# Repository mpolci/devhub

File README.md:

# devhub — hub USB "intelligente" per lo sviluppo hardware

Hub USB da banco pensato per chi sviluppa dispositivi a microcontrollore collegati via USB.
Oltre alle porte downstream espone all'host un **dispositivo di controllo** (USB HID) con cui
il PC può:

- **staccare e riattaccare fisicamente** ogni porta (alimentazione VBUS e linee dati D+/D-),
  per resettare un dispositivo bloccato anche quando il reset via USB non funziona;
- **leggere lo stato** di ogni porta (abilitata/disabilitata, ciclo in corso, guasti hardware);
- **comandare un relè ausiliario** con uscita su due boccole a banana (es. per sezionare
  l'alimentazione esterna del dispositivo in prova o chiudere un contatto di reset).

## Caratteristiche previste (v1)

| Voce | Scelta v1 |
|---|---|
| Porte downstream | 4 × USB-C |
| Velocità | USB 2.0 Hi-Speed (480 Mbit/s) |
| Alimentazione per porta | 5 V, fino a 2 A sulla singola porta USB-C, circa 2,4 A totali stimati, con limitazione di corrente e sezionamento per porta |
| Sezionamento | VBUS **e** D+/D− con unico comando logico; ammessa la sequenza interna del controller |
| Ciclo di spegnimento/riaccensione porta | Ciclo temporizzato con scarica attiva, durata configurabile; default indicativo 1 s da validare, senza verifica della tensione |
| Indicazione porta | Un LED dal MCU: spento, acceso fisso, lampeggiante per guasto |
| Alimentazione hub | richiesti alimentatore USB-C 5 V / 3 A senza negoziazione PD e cavo adeguato; nessuna verifica delle CC |
| Upstream (verso il PC) | USB-C (USB 2.0) |
| Controllo | STM32G0B1 su porta interna dell'hub, interfaccia USB HID senza driver + CLI Python |
| Relè ausiliari | 1 × SPDT su due boccole a banana COM/NC, contatti max 16 V / 3 A |
| Misure | Corrente e carica erogata per porta, temperatura del controllo; nessuna tensione |
| Pannello | 5 pulsanti; 5 LED: uno per porta USB, con lampeggio guasti, e uno di host collegato |

I 3 A d'ingresso comprendono anche i consumi interni: un sovraccarico complessivo può
interrompere l'intero hub. Il ciclo non verifica elettricamente lo spegnimento e riguarda
l'alimentazione fornita dalla porta; per riavviare schede autoalimentate servono relè o reset.

Le motivazioni delle scelte (in particolare USB 2.0 invece di USB 3 e il non sezionare GND)
sono in [docs/architettura.md](docs/architettura.md).

## Struttura del repository

```
docs/        requisiti, architettura, protocollo di controllo, domande aperte
hardware/    progetto KiCad (schema, PCB, BOM)
firmware/    firmware del MCU di controllo
host/        libreria Python e strumento da riga di comando per il PC, skill per agenti AI
```

## Documenti

- [docs/requisiti.md](docs/requisiti.md) — cosa deve fare il dispositivo
- [docs/architettura.md](docs/architettura.md) — schema a blocchi, scelte progettuali, componenti candidati, bilancio di potenza
- [docs/componenti.md](docs/componenti.md) — componenti candidati, package, fornitori, classe JLCPCB
- [docs/protocollo-controllo.md](docs/protocollo-controllo.md) — bozza del protocollo HID tra PC e hub
- [docs/regole-pcb.md](docs/regole-pcb.md) — stackup, piste, USB, alimentazione, piazzamento e verifiche di produzione
- [docs/pinout-mcu.md](docs/pinout-mcu.md) — piedinatura del MCU e note per il firmware
- [docs/domande-aperte.md](docs/domande-aperte.md) — decisioni ancora da prendere

## Licenze

- **Hardware** (`hardware/`): [CERN-OHL-W 2.0](hardware/LICENSE).
- **Firmware, libreria e CLI, documentazione** (tutto il resto): [MIT](LICENSE).

## Stato

Requisiti semplificati definiti (D60–D66). Hub USB2517I-JZX, MCU STM32G0B1CEU6 in UFQFPN48
(D78), due UCS2114-1-V/LX con due bus I²C e quattro PI3USB4002A per le porte (D75), con
DigiKey come fornitore di riferimento.

Schema elettrico v0.3 allineato ai requisiti (D79–D83); PCB 100 × 100 mm a quattro strati (D84)
completo (D84–D95, vedi [hardware/README.md](hardware/README.md)). Il prototipo Rev A è
montato e funziona: corretti alcuni difetti di saldatura, nessuna modifica al PCB.

Firmware ([firmware/README.md](firmware/README.md)) e libreria Python con CLI
([host/README.md](host/README.md)) sono scritti secondo D96–D103 e il protocollo 0.1. Sul
prototipo sono verificati hub configurato via SMBus, aggiornamento via DFU attraverso il
hub, le quattro porte (accensione, spegnimento, ciclo, enumerazione di un dispositivo),
relè, LED, pulsanti, default in flash, eventi, watchdog, temperatura del MCU e corrente delle porte. Restano le misure con strumenti:
durata della scarica e del ciclo, sfasamento delle accensioni, guasti reali e ritorno di
alimentazione (D98), tempi I²C, corrente dei LED, transitori al reset e in DFU. Dopo le misure
il protocollo passerà alla versione 1.0.

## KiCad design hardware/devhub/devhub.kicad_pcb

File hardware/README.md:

# hardware

Progetto KiCad 10 (schema, PCB, BOM) dell'hub.

```
hardware/devhub/        progetto KiCad: devhub.kicad_pro, devhub.kicad_sch (radice), i fogli e devhub.kicad_pcb
hardware/lib/           devhub.kicad_sym: simboli non presenti nelle librerie standard (USB2517, PI3USB4002A, TPS259470A, UCS2114) e SMAJ20A con pin K/A espliciti
hardware/devhub/production/   file di produzione Rev A: gerber (devhub_A.zip), BOM, posizioni, designatori, netlist IPC
hardware/devhub/jlcpcb/       database del plugin di esportazione per JLCPCB
```

## Stato: schema v0.3, PCB Rev A

Lo schema applica i [requisiti semplificati](../docs/requisiti.md) e le decisioni D60–D95
(dettaglio in D79): quattro porte USB-C, un relè, cinque pulsanti, un LED per porta, LED del relè e di host. Il PCB
da 100 × 100 mm è sbrogliato e prodotto come Rev A (vedi sotto).

Il prototipo Rev A è montato e collaudato con il firmware. Alimentazioni, hub, MCU, controller
delle porte, interruttori dati, LED, pulsanti e relè funzionano. Gli unici difetti trovati
erano saldature di U3 (MCU), U4 e U5 (UCS2114), J401 (connettore della porta 4) e U401 (switch
dati della porta 4), tutte ripassate. Nel PCB le reti sono corrette e non servono modifiche.
Dettaglio delle prove in
[../docs/lavorazioni/piano-firmware.md](../docs/lavorazioni/piano-firmware.md).

Simboli delle librerie standard di KiCad più quelli di progetto in `lib/`; fogli gerarchici riusati per le
porte. Componenti vicini collegati a filo, ma ogni rete ha comunque un nome esplicito: etichette
locali per le reti interne a un foglio, globali per quelle che passano tra fogli, gerarchiche per
le porte. Passa l'ERC di `kicad-cli` con zero violazioni.

Fogli:

| Foglio | Contenuto |
|---|---|
| `power_in` | USB-C di alimentazione a 5 V, Rd 5,1 kΩ su CC1/CC2 senza lettura, TVS, eFuse TPS259470A (U13), bulk, Schottky D2, LDO 3,3 V (AP7361C-33E, SOT-223) |
| `hub` | USB2517, USB-C upstream con ESD, quarzo, RBIAS, supervisore di reset (U12) in wired-OR con il MCU, strap di configurazione, VBUS_DET; DS5, DS7 e OCS5_N non collegati. Switch VBUS: 2 × UCS2114-1-V/LX (U4 porte 1-2 su I2C1, U5 porte 3-4 su I2C2), strap COMM_ILIM 27 kΩ, disaccoppiamenti, pull-up degli ALERT# |
| `mcu` | STM32G0B1CEU6 (UFQFPN48), decoupling, SWD (J4) e UART (J9) collegati a filo, pull-up dei due bus I²C, pull-down degli EN porta, pull-down dei DBCC dell'UCPD, LED di host collegato |
| `port_c` ×4 | connettore, switch dati PI3USB4002A (con protezione ESD integrata), condensatori VBUS, Rp 56 kΩ, LED verde dal MCU, pulsante |
| `relays` | ULN2003V12 (3 canali in parallelo), G5Q-1, ponticello NC/NO, boccole Cliff FCR7350, snubber DNP, pulsante SW1, LED del relè D90 |

Piedinatura del MCU: [../docs/pinout-mcu.md](../docs/pinout-mcu.md).

Connettori USB decisi (D18): GCT USB4105-GF-A per tutti gli USB-C.

Quarzo deciso (D19): YXC X322524MOB4SI, C_L 12 pF, C22/C23 da 15 pF.

Footprint locali assegnati dalla libreria `lcsc_footprints` (`devhub/libs/footprints.pretty`):
- U13 TPS259470A: `C3662799_VQFN-10_L2_0-W2_0-P0_45-TL`;
- U101–U401 PI3USB4002A: `C3657361_UQFN-10_L2_0-W1_5-P0_50-TL`;
- U4, U5 UCS2114: `UCS2114_VQFN-20_3x3mm_P0.5mm`;
- U2 USB2517: `QFN-64-1EP_9x9mm_P0.5mm_EP4.7x4.7mm_ThermalVias_0.3mm` (D50).

Le piazzole di U13 e U101–U401 sono quelle generate da LCSC, non copiate dai land pattern dei
costruttori: nel PI3USB4002A le laterali sono 0,665 × 0,28 mm invece di 0,53 × 0,25 (più lunghe
verso l'esterno, stesso bordo interno), nel TPS259470A le coordinate coincidono con l'esempio TI
RPW0010A entro ~0,05 mm. Differenze accettate: il bordo esterno più lungo aiuta la saldatura ad
aria calda. Courtyard ridisegnati a 0,25 mm dalle piazzole (quelli importati erano più piccoli
del rame).

L'impronta dell'UCS2114 segue il land pattern Microchip C04-2421 Rev C (datasheet
DS20005743B): 20 piazzole 0,25 × 0,5 mm su C1 = C2 = 2,9 mm, otto angoli smussati di 0,1 mm,
area termica 2,00 × 1,13 mm coperta da solder mask e collegata al pin 17 (GND), con 6 via
0,3/0,5 mm. Il package non ha pad esposto. Modello 3D: quello di KiCad per UFQFPN-20 3 × 3 mm,
come segnaposto (stesse dimensioni in pianta, altezza diversa).

J4 (SWD, Samtec FTSH-105-01-L-DV-K) usa l'impronta generica
`PinHeader_2x05_P1.27mm_Vertical_SMD`: KiCad non ha quella Samtec, e rispetto al land pattern
Samtec le piazzole sono più corte (2,40 invece di 2,79 mm, ingombro 6,30 invece di 6,86 mm), con
stesso passo e stessa larghezza. Accettata: è un connettore di debug saldato a mano.

I footprint usano i modelli in `devhub/libs/3dmodels` con percorsi relativi al progetto.
Il modello C3657361 è un segnaposto dell'importatore, non una rappresentazione del package.

BOM: i simboli hanno i campi `warehouse` (ID del magazzino), `lcsc`, `mouser` e `digikey`;
confronto dei costi della v0.2 in [../docs/confronto-costi.md](../docs/confronto-costi.md). Su
Mouser mancano le boccole Cliff (campo vuoto). Da completare: U4/U5 (nessun codice fornitore),
U3 su Mouser e LCSC, R60/R61 su LCSC.

Per l'ERC da riga di comando:

```bash
/Applications/KiCad/KiCad.app/Contents/MacOS/kicad-cli sch erc --severity-all --output /tmp/erc.rpt hardware/devhub/devhub.kicad_sch
```

## PCB

Regole di progettazione: [stackup, routing e verifiche PCB](../docs/regole-pcb.md), configurate
nel progetto: stackup nel PCB, vincoli e netclass in `devhub.kicad_pro`, regole personalizzate in
`devhub.kicad_dru`.

`devhub.kicad_pcb`: 4 strati, profilo **100 × 100 mm** con angoli R3 (D84), allineato allo schema
v0.3 (parità senza differenze). Vista dall'alto, fronte (lato banco) in basso; u dal bordo
sinistro, v dal bordo frontale.

| Cosa | Faccia | Posizione (u, v in mm) |
|---|---|---|
| J5 COM, J6 NC boccole | inferiore | u = 10 e 27; corpo a v = 11,85 come prima, manicotto a filo della faccia esterna della parete |
| J401, J301, J201, J101 USB-C (porte 4…1) | inferiore | u = 46, 61, 76, 91; faccia d'innesto a filo del bordo frontale |
| LED delle porte D402…D102 (verdi) | superiore | in asse con la porta, v = 2 |
| D90 LED relè | superiore | u = 18,5, v = 2, sopra la coppia di boccole (D90) |
| D93 LED host | superiore | u = 10, v = 90, sul retro a sinistra di J1, con R93 a u = 15 (D90) |
| SW1, SW401…SW101 pulsanti | superiore | v = 14,5 (D87); SW1 al centro delle boccole (u = 18,5), gli altri in asse con le porte |
| J1 alimentazione, J2 upstream | inferiore | u = 24 e 82, a filo del bordo posteriore |
| H1–H4 fori M3 | — | H1 (20; 44,2) a destra del relè K1, dentro l'area dei contatti (D95), H2 (95,5; 28), H3 (4,5; 95,5), H4 (95,5; 95,5); anello di rame da 6,4 mm, senza rete |

Gruppi funzionali sulla faccia inferiore, traslati dal piazzamento v0.2 con le rispettive aree
di regola: porte con switch dati e condensatori dietro i connettori; U4/U5 UCS2114 dietro i
pulsanti, fra le porte che servono; relè K1, driver U9 e ponticello a sinistra dietro le boccole;
MCU al centro; hub con quarzo e disaccoppiamenti al centro-destra; alimentazione (eFuse, LDO,
bulk) dietro a sinistra; upstream con ESD e VBUS_DET dietro a destra; J4 (SWD) e J9 (UART) sul
retro, fra J1 e J2.

Sbroglio completo. Piani: GND su In2.Cu (`GND_In2`), +3V3 su In1.Cu (`3V3_In1`) con isole VBUS
sotto i connettori e una zona +5V lungo il bordo frontale verso U4/U5 (D93). Il PCB va
modificato in KiCad dallo stato corrente, non rigenerato.

Per il controllo di parità con lo schema da riga di comando:

```bash
/Applications/KiCad/KiCad.app/Contents/MacOS/kicad-cli pcb drc --schematic-parity --severity-all --output /tmp/drc.rpt hardware/devhub/devhub.kicad_pcb
```

I datasheet dei componenti sono in `../datasheets/` (fuori dal repository: non ridistribuibili).
Da scaricare a mano dal sito ST, che blocca i download automatici: datasheet STM32G0B1, reference
manual RM0444, datasheet USBLC6-2.

Licenza: CERN-OHL-W 2.0, vedi [LICENSE](LICENSE).

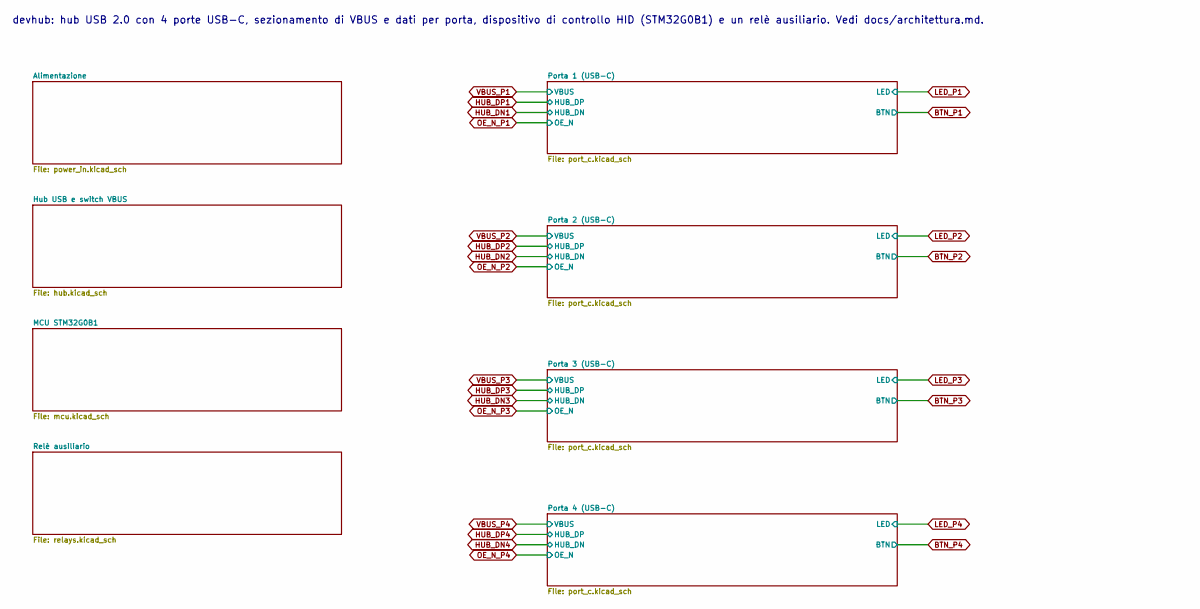
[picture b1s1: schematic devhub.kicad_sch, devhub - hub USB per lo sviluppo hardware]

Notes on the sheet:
devhub: hub USB 2.0 con 4 porte USB-C, sezionamento di VBUS e dati per porta, dispositivo di controllo HID (STM32G0B1) e un relè ausiliario. Vedi docs/architettura.md.

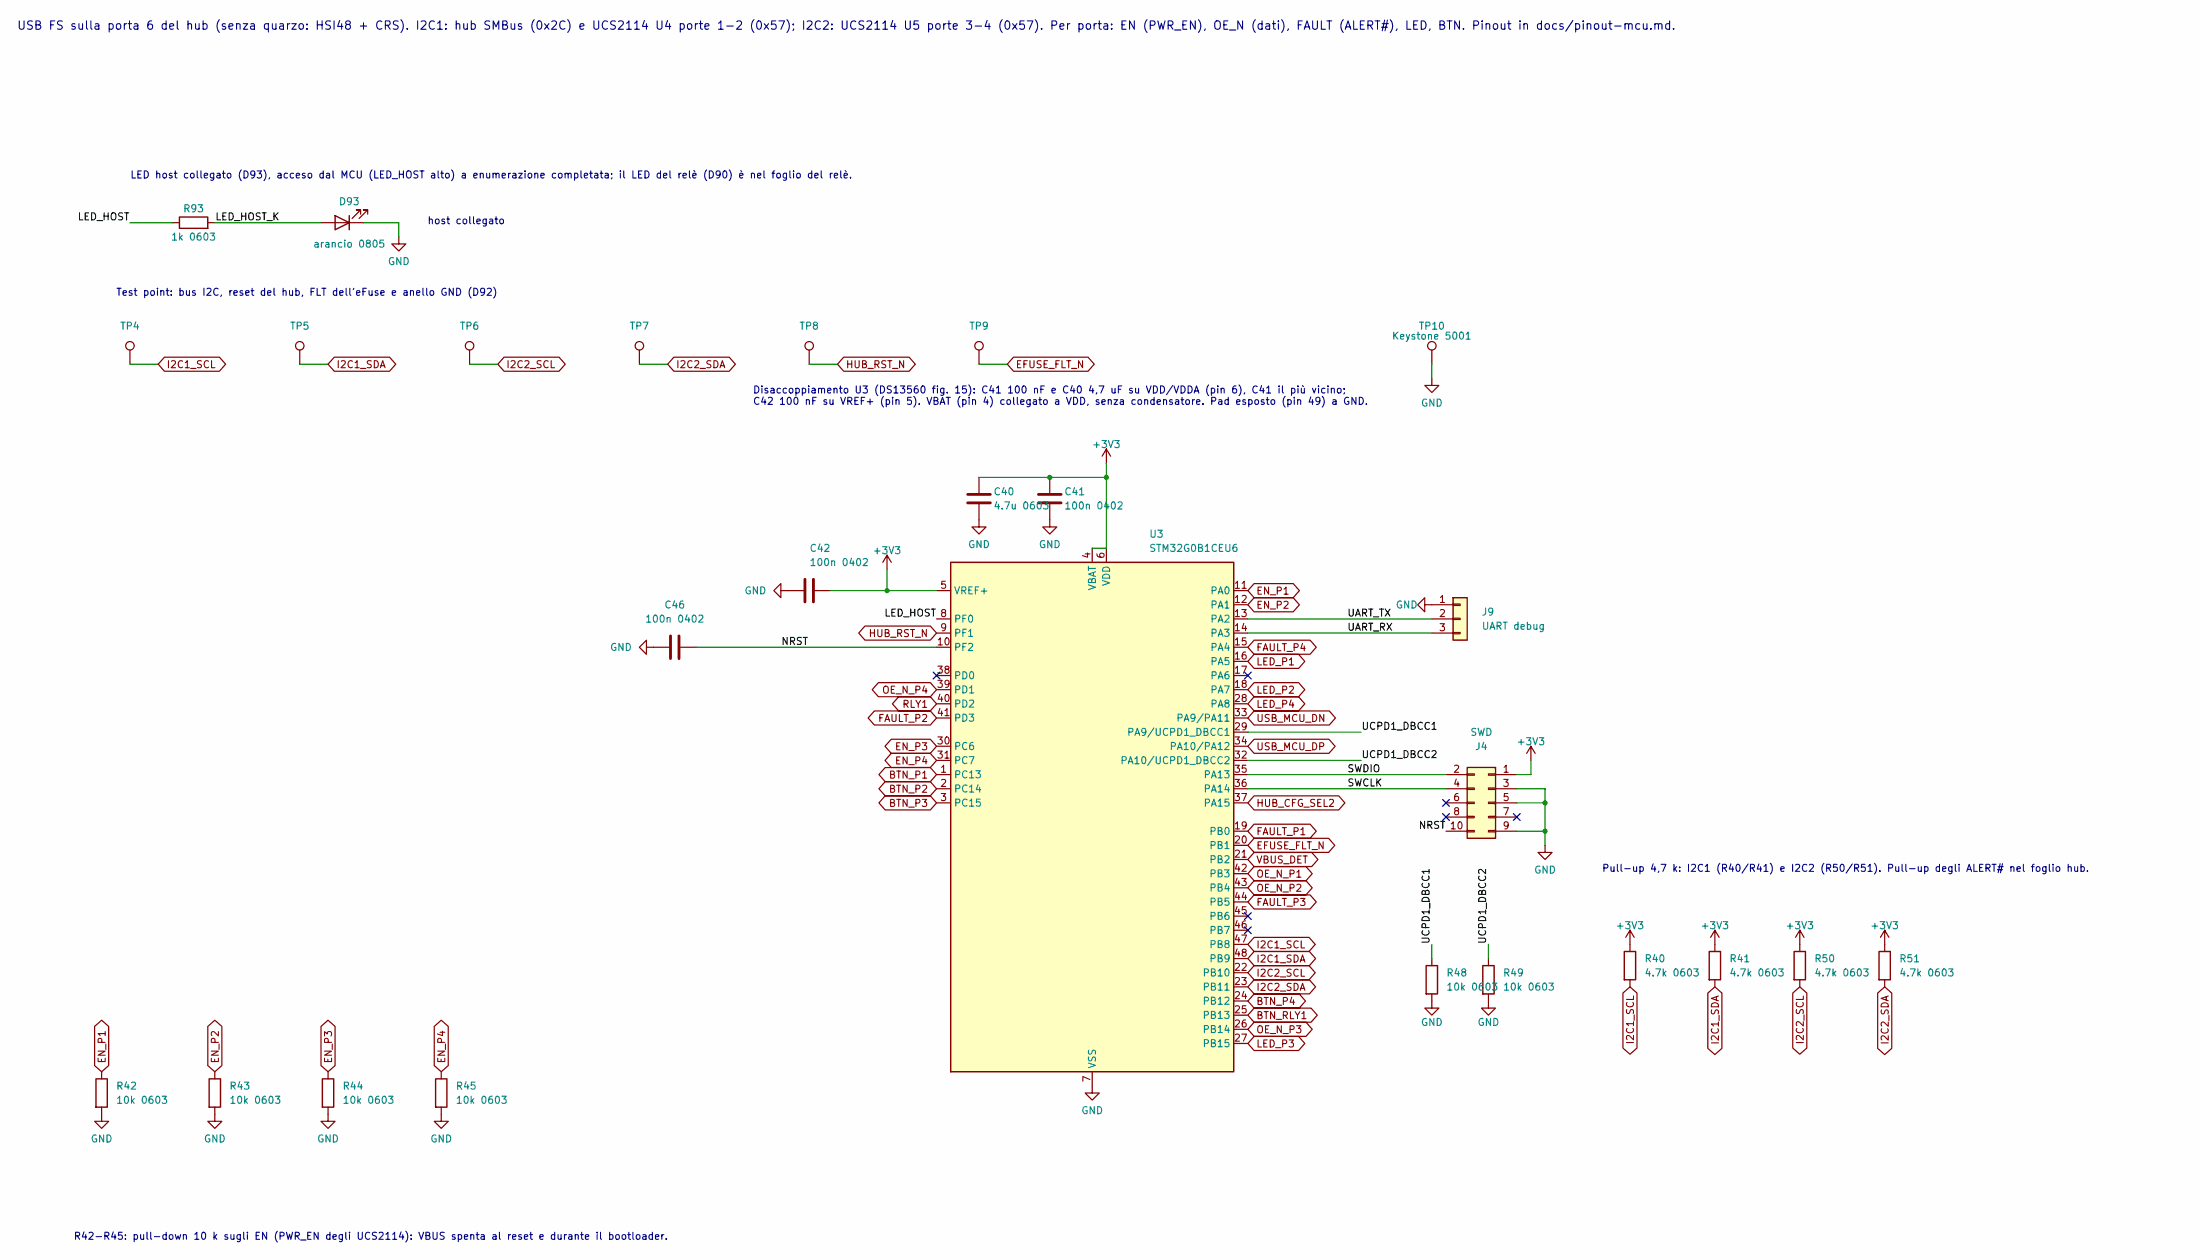
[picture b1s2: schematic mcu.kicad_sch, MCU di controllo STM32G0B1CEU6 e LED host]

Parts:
C40: 4.7u 0603; C_0603_1608Metric; MPN lcsc CL10A475KO8NNNC; lcsc C19666
C41, C42, C46: 100n 0402; C_0402_1005Metric; MPN lcsc CC0402KRX7R7BB104; lcsc C60474
D93: arancio 0805; LED_0805_2012Metric; MPN lcsc LTST-C171KFKT; lcsc C284932
J4: SWD; PinHeader_2x05_P1.27mm_Vertical_SMD; MPN lcsc FTSH-105-01-L-DV-K; lcsc C5155080
J9: UART debug; PinHeader_1x03_P2.54mm_Vertical; MPN lcsc 2.54-1*3P; lcsc C49257
R40, R41, R50, R51: 4.7k 0603; R_0603_1608Metric; MPN lcsc RC0603FR-074K7L; lcsc C99782
R42, R43, R44, R45, R48, R49: 10k 0603; R_0603_1608Metric; MPN lcsc FRC0603F1002TS; lcsc C2906982
R93: 1k 0603; R_0603_1608Metric; MPN lcsc 0603WAF1001T5E; lcsc C21190
TP4: I2C1_SCL; TestPoint_Pad_D1.5mm
TP5: I2C1_SDA; TestPoint_Pad_D1.5mm
TP6: I2C2_SCL; TestPoint_Pad_D1.5mm
TP7: I2C2_SDA; TestPoint_Pad_D1.5mm
TP8: HUB_RST_N; TestPoint_Pad_D1.5mm
TP9: EFUSE_FLT_N; TestPoint_Pad_D1.5mm
TP10: Keystone 5001; TestPoint_Keystone_5000-5004_Miniature; MPN mouser 5001; lcsc C238122
U3: STM32G0B1CEU6; QFN-48-1EP_7x7mm_P0.5mm_EP5.6x5.6mm; MPN lcsc STM32G0B1CEU6; lcsc C2829190

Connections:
+3V3: C40.1, C41.1, C42.1, J4.1, R40.1, R41.1, R50.1, R51.1, U3.4 (VBAT), U3.5 (VREF+), U3.6 (VDD); also elsewhere on the board
/MCU STM32G0B1/LED_HOST: R93.1, U3.8 (PF0)
/MCU STM32G0B1/LED_HOST_K: D93.2 (A), R93.2
/MCU STM32G0B1/NRST: C46.1, J4.10, U3.10 (PF2)
/MCU STM32G0B1/SWCLK: J4.4, U3.36 (PA14)
/MCU STM32G0B1/SWDIO: J4.2, U3.35 (PA13)
/MCU STM32G0B1/UART_RX: J9.3, U3.14 (PA3)
/MCU STM32G0B1/UART_TX: J9.2, U3.13 (PA2)
/MCU STM32G0B1/UCPD1_DBCC1: R48.1, U3.29 (PA9/UCPD1_DBCC1)
/MCU STM32G0B1/UCPD1_DBCC2: R49.1, U3.32 (PA10/UCPD1_DBCC2)
BTN_P1: U3.1 (PC13); also elsewhere on the board
BTN_P2: U3.2 (PC14); also elsewhere on the board
BTN_P3: U3.3 (PC15); also elsewhere on the board
BTN_P4: U3.24 (PB12); also elsewhere on the board
BTN_RLY1: U3.25 (PB13); also elsewhere on the board
EFUSE_FLT_N: TP9.1 (1_1), U3.20 (PB1); also elsewhere on the board
EN_P1: R42.1, U3.11 (PA0); also elsewhere on the board
EN_P2: R43.1, U3.12 (PA1); also elsewhere on the board
EN_P3: R44.1, U3.30 (PC6); also elsewhere on the board
EN_P4: R45.1, U3.31 (PC7); also elsewhere on the board
FAULT_P1: U3.19 (PB0); also elsewhere on the board
FAULT_P2: U3.41 (PD3); also elsewhere on the board
FAULT_P3: U3.44 (PB5); also elsewhere on the board
FAULT_P4: U3.15 (PA4); also elsewhere on the board
GND: C40.2, C41.2, C42.2, C46.2, D93.1 (K), J4.3, J4.5, J4.9, J9.1, R42.2, R43.2, R44.2, R45.2, R48.2, R49.2, TP10.1 (1_1), U3.7 (VSS), U3.49 (VSS); also elsewhere on the board
HUB_CFG_SEL2: U3.37 (PA15); also elsewhere on the board
HUB_RST_N: TP8.1 (1_1), U3.9 (PF1); also elsewhere on the board
I2C1_SCL: R40.2, TP4.1 (1_1), U3.47 (PB8); also elsewhere on the board
I2C1_SDA: R41.2, TP5.1 (1_1), U3.48 (PB9); also elsewhere on the board
I2C2_SCL: R50.2, TP6.1 (1_1), U3.22 (PB10); also elsewhere on the board
I2C2_SDA: R51.2, TP7.1 (1_1), U3.23 (PB11); also elsewhere on the board
LED_P1: U3.16 (PA5); also elsewhere on the board
LED_P2: U3.18 (PA7); also elsewhere on the board
LED_P3: U3.27 (PB15); also elsewhere on the board
LED_P4: U3.28 (PA8); also elsewhere on the board
OE_N_P1: U3.42 (PB3); also elsewhere on the board
OE_N_P2: U3.43 (PB4); also elsewhere on the board
OE_N_P3: U3.26 (PB14); also elsewhere on the board
OE_N_P4: U3.39 (PD1); also elsewhere on the board
RLY1: U3.40 (PD2); also elsewhere on the board
USB_MCU_DN: U3.33 (PA9/PA11); also elsewhere on the board
USB_MCU_DP: U3.34 (PA10/PA12); also elsewhere on the board
VBUS_DET: U3.21 (PB2); also elsewhere on the board

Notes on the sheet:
Disaccoppiamento U3 (DS13560 fig. 15): C41 100 nF e C40 4,7 uF su VDD/VDDA (pin 6), C41 il più vicino; C42 100 nF su VREF+ (pin 5). VBAT (pin 4) collegato a VDD, senza condensatore. Pad esposto (pin 49) a GND.
Test point: bus I2C, reset del hub, FLT dell'eFuse e anello GND (D92)
USB FS sulla porta 6 del hub (senza quarzo: HSI48 + CRS). I2C1: hub SMBus (0x2C) e UCS2114 U4 porte 1-2 (0x57); I2C2: UCS2114 U5 porte 3-4 (0x57). Per porta: EN (PWR_EN), OE_N (dati), FAULT (ALERT#), LED, BTN. Pinout in docs/pinout-mcu.md.
Pull-up 4,7 k: I2C1 (R40/R41) e I2C2 (R50/R51). Pull-up degli ALERT# nel foglio hub.
host collegato
LED host collegato (D93), acceso dal MCU (LED_HOST alto) a enumerazione completata; il LED del relè (D90) è nel foglio del relè.
R42-R45: pull-down 10 k sugli EN (PWR_EN degli UCS2114): VBUS spenta al reset e durante il bootloader.

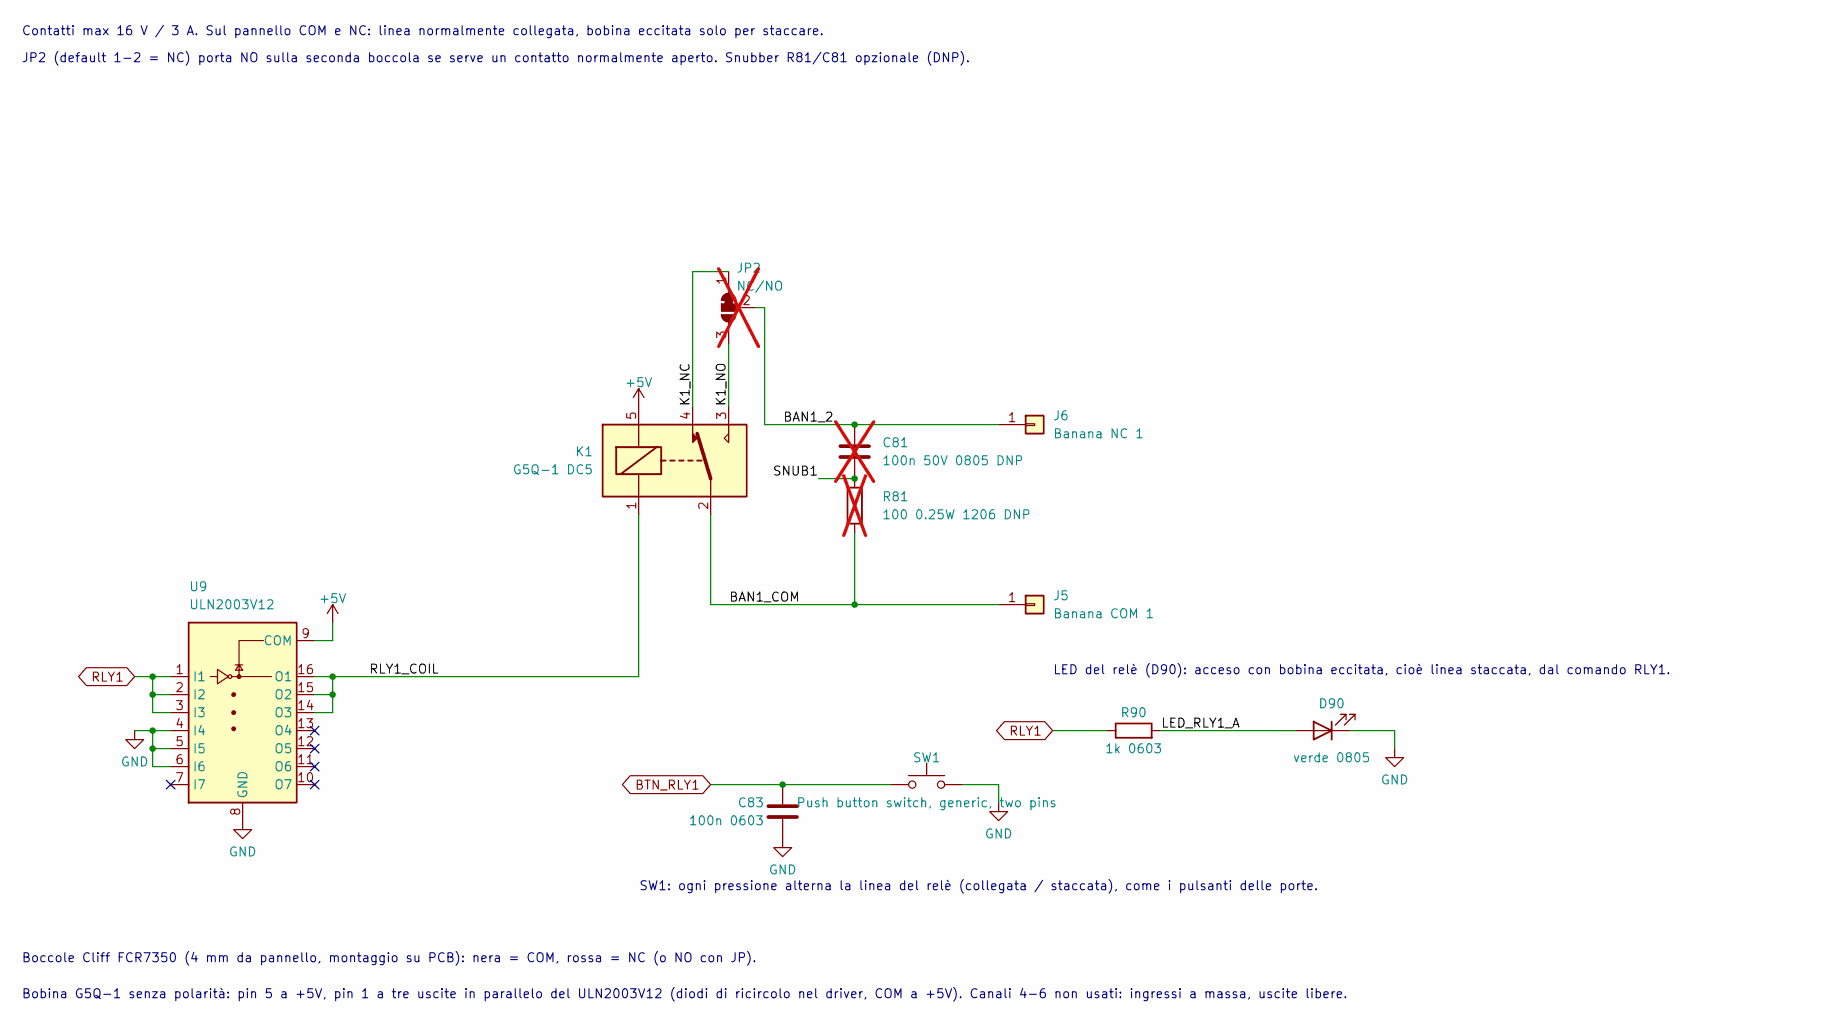
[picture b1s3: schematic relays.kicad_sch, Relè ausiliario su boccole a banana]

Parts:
C81: 100n 50V 0805 DNP; C_0805_2012Metric; MPN lcsc 0805B104K500CT; lcsc C83055; not fitted
C83: 100n 0603; C_0603_1608Metric; MPN lcsc CL10B104KB8NNNC; lcsc C1591
D90: verde 0805; LED_0805_2012Metric; MPN lcsc LTST-C171GKT; lcsc C913075
J5: Banana COM 1; Banana_Cliff_FCR7350B_S16N-PC_Horizontal; MPN digikey FCR7350B; digikey 4654-FCR7350B-ND
J6: Banana NC 1; Banana_Cliff_FCR7350R_S16N-PC_Horizontal; MPN lcsc FCR7350R; lcsc C6041087
JP2: NC/NO; SolderJumper-3_P2.4mm_Bridged12_Pad2.0x3.0mm; not fitted
K1: G5Q-1 DC5; Relay_SPDT_Omron-G5Q-1; MPN lcsc G5Q-14 DC5; lcsc C397241
R81: 100 0.25W 1206 DNP; R_1206_3216Metric; MPN lcsc RC1206FR-07100RL; lcsc C137392; not fitted
R90: 1k 0603; R_0603_1608Metric; MPN lcsc 0603WAF1001T5E; lcsc C21190
SW1: Push button switch, generic, two pins; SW_SPST_PTS645Sx43SMTR92; MPN lcsc PTS645SL70SMTR92 LFS; lcsc C285485
U9: ULN2003V12; SOIC-16_3.9x9.9mm_P1.27mm; MPN lcsc ULN2003V12DR; lcsc C94916

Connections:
+5V: K1.5, U9.9 (COM); also elsewhere on the board
/Relè ausiliario/BAN1_2: C81.1, J6.1 (Pin_1_1), JP2.2 (C)
/Relè ausiliario/BAN1_COM: J5.1 (Pin_1_1), K1.2, R81.2
/Relè ausiliario/K1_NC: JP2.1 (A), K1.4
/Relè ausiliario/K1_NO: JP2.3 (B), K1.3
/Relè ausiliario/LED_RLY1_A: D90.2 (A), R90.2
/Relè ausiliario/RLY1_COIL: K1.1, U9.14 (O3), U9.15 (O2), U9.16 (O1)
/Relè ausiliario/SNUB1: C81.2, R81.1
BTN_RLY1: C83.1, SW1.1; also elsewhere on the board
GND: C83.2, D90.1 (K), SW1.2, U9.4 (I4), U9.5 (I5), U9.6 (I6), U9.8 (GND); also elsewhere on the board
RLY1: R90.1, U9.1 (I1), U9.2 (I2), U9.3 (I3); also elsewhere on the board

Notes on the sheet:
Bobina G5Q-1 senza polarità: pin 5 a +5V, pin 1 a tre uscite in parallelo del ULN2003V12 (diodi di ricircolo nel driver, COM a +5V). Canali 4-6 non usati: ingressi a massa, uscite libere.
JP2 (default 1-2 = NC) porta NO sulla seconda boccola se serve un contatto normalmente aperto. Snubber R81/C81 opzionale (DNP).
Boccole Cliff FCR7350 (4 mm da pannello, montaggio su PCB): nera = COM, rossa = NC (o NO con JP).
Contatti max 16 V / 3 A. Sul pannello COM e NC: linea normalmente collegata, bobina eccitata solo per staccare.
LED del relè (D90): acceso con bobina eccitata, cioè linea staccata, dal comando RLY1.
SW1: ogni pressione alterna la linea del relè (collegata / staccata), come i pulsanti delle porte.

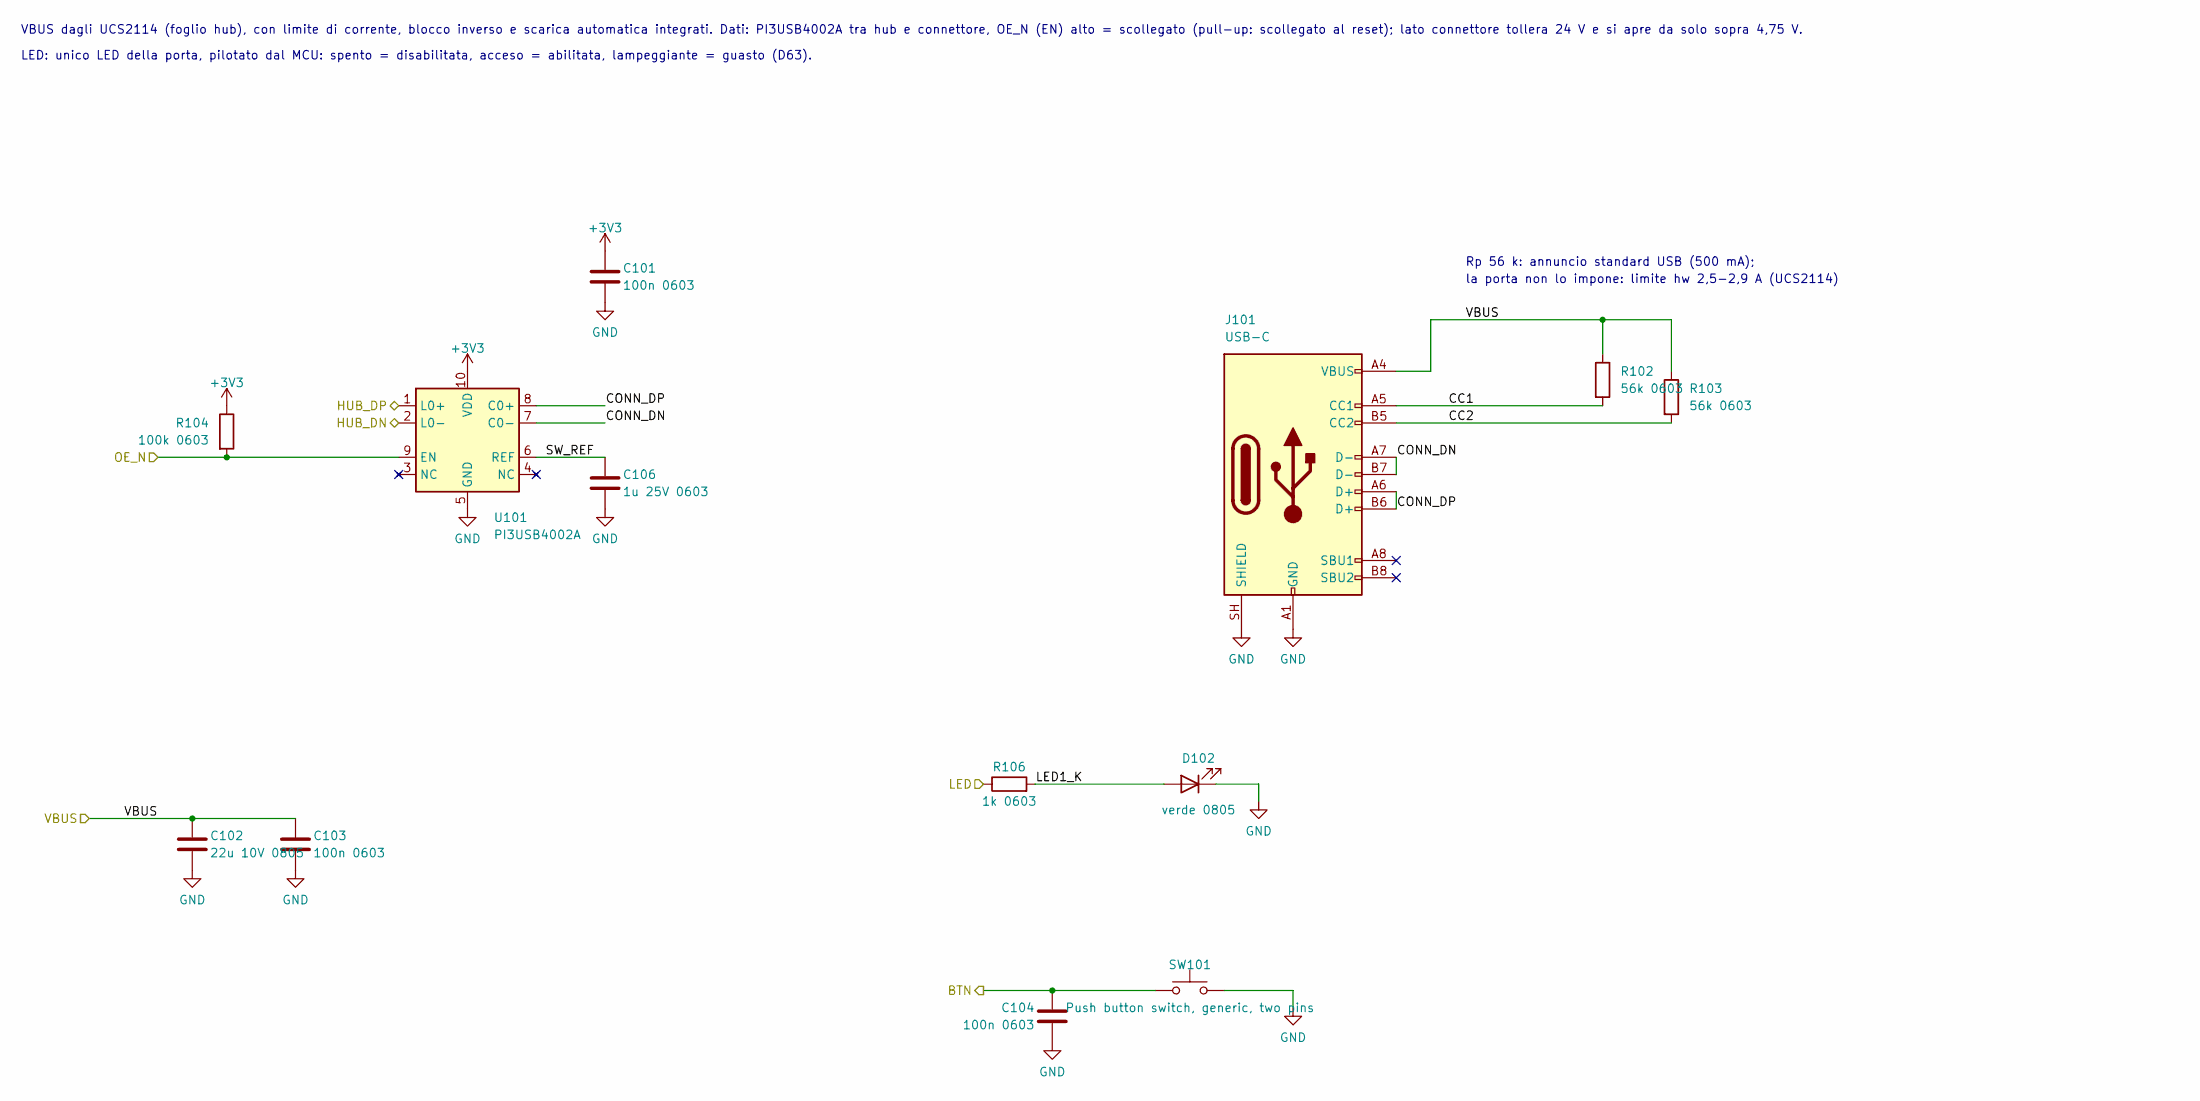
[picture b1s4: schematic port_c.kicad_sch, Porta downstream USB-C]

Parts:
C101, C103, C104: 100n 0603; C_0603_1608Metric; MPN lcsc CL10B104KB8NNNC; lcsc C1591
C102: 22u 10V 0805; C_0805_2012Metric; MPN lcsc GRM21BZ71A226ME15L; lcsc C907991
C106: 1u 25V 0603; C_0603_1608Metric; MPN lcsc CL10B105KA8NNNC; lcsc C29936
D102: verde 0805; LED_0805_2012Metric; MPN lcsc LTST-C171GKT; lcsc C913075
J101: USB-C; USB_C_Receptacle_GCT_USB4105-xx-A_16P_TopMnt_Horizontal; MPN lcsc USB4105-GF-A; lcsc C3020560
R102, R103: 56k 0603; R_0603_1608Metric; MPN lcsc RC0603FR-0756KL; lcsc C114630
R104: 100k 0603; R_0603_1608Metric; MPN lcsc FRC0603F1003TS; lcsc C2906980
R106: 1k 0603; R_0603_1608Metric; MPN lcsc 0603WAF1001T5E; lcsc C21190
SW101: Push button switch, generic, two pins; SW_SPST_PTS645Sx43SMTR92; MPN lcsc PTS645SL70SMTR92 LFS; lcsc C285485
U101: PI3USB4002A; C3657361_UQFN-10_L2_0-W1_5-P0_50-TL; MPN lcsc PI3USB4002AZUAEX; lcsc C6735706

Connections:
+3V3: C101.1, R104.1, U101.10 (VDD); also elsewhere on the board
/Porta 1 (USB-C)/CC1: J101.A5 (CC1), R102.2
/Porta 1 (USB-C)/CC2: J101.B5 (CC2), R103.2
/Porta 1 (USB-C)/CONN_DN: J101.A7 (D-), J101.B7 (D-), U101.7 (C0-)
/Porta 1 (USB-C)/CONN_DP: J101.A6 (D+), J101.B6 (D+), U101.8 (C0+)
/Porta 1 (USB-C)/LED1_K: D102.2 (A), R106.2
/Porta 1 (USB-C)/SW_REF: C106.1, U101.6 (REF)
BTN_P1: C104.1, SW101.1; also elsewhere on the board
GND: C101.2, C102.2, C103.2, C104.2, C106.2, D102.1 (K), J101.A1 (GND), J101.A12 (GND), J101.B1 (GND), J101.B12 (GND), J101.SH (SHIELD), SW101.2, U101.5 (GND); also elsewhere on the board
HUB_DN1: U101.2 (L0-); also elsewhere on the board
HUB_DP1: U101.1 (L0+); also elsewhere on the board
LED_P1: R106.1; also elsewhere on the board
OE_N_P1: R104.2, U101.9 (EN); also elsewhere on the board
VBUS_P1: C102.1, C103.1, J101.A4 (VBUS), J101.A9 (VBUS), J101.B4 (VBUS), J101.B9 (VBUS), R102.1, R103.1; also elsewhere on the board

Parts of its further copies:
C201, C203, C204, C301, C303, C304, C401, C403, C404: 100n 0603; C_0603_1608Metric; MPN lcsc CL10B104KB8NNNC; lcsc C1591
C202, C302, C402: 22u 10V 0805; C_0805_2012Metric; MPN lcsc GRM21BZ71A226ME15L; lcsc C907991
C206, C306, C406: 1u 25V 0603; C_0603_1608Metric; MPN lcsc CL10B105KA8NNNC; lcsc C29936
D202, D302, D402: verde 0805; LED_0805_2012Metric; MPN lcsc LTST-C171GKT; lcsc C913075
J201, J301, J401: USB-C; USB_C_Receptacle_GCT_USB4105-xx-A_16P_TopMnt_Horizontal; MPN lcsc USB4105-GF-A; lcsc C3020560
R202, R203, R302, R303, R402, R403: 56k 0603; R_0603_1608Metric; MPN lcsc RC0603FR-0756KL; lcsc C114630
R204, R304, R404: 100k 0603; R_0603_1608Metric; MPN lcsc FRC0603F1003TS; lcsc C2906980
R206, R306, R406: 1k 0603; R_0603_1608Metric; MPN lcsc 0603WAF1001T5E; lcsc C21190
SW201, SW301, SW401: Push button switch, generic, two pins; SW_SPST_PTS645Sx43SMTR92; MPN lcsc PTS645SL70SMTR92 LFS; lcsc C285485
U201, U301, U401: PI3USB4002A; C3657361_UQFN-10_L2_0-W1_5-P0_50-TL; MPN lcsc PI3USB4002AZUAEX; lcsc C6735706

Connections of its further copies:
+3V3: C201.1, C301.1, C401.1, R204.1, R304.1, R404.1, U201.10 (VDD), U301.10 (VDD), U401.10 (VDD); also elsewhere on the board
/Porta 2 (USB-C)/CC1: J201.A5 (CC1), R202.2
/Porta 2 (USB-C)/CC2: J201.B5 (CC2), R203.2
/Porta 2 (USB-C)/CONN_DN: J201.A7 (D-), J201.B7 (D-), U201.7 (C0-)
/Porta 2 (USB-C)/CONN_DP: J201.A6 (D+), J201.B6 (D+), U201.8 (C0+)
/Porta 2 (USB-C)/LED1_K: D202.2 (A), R206.2
/Porta 2 (USB-C)/SW_REF: C206.1, U201.6 (REF)
/Porta 3 (USB-C)/CC1: J301.A5 (CC1), R302.2
/Porta 3 (USB-C)/CC2: J301.B5 (CC2), R303.2
/Porta 3 (USB-C)/CONN_DN: J301.A7 (D-), J301.B7 (D-), U301.7 (C0-)
/Porta 3 (USB-C)/CONN_DP: J301.A6 (D+), J301.B6 (D+), U301.8 (C0+)
/Porta 3 (USB-C)/LED1_K: D302.2 (A), R306.2
/Porta 3 (USB-C)/SW_REF: C306.1, U301.6 (REF)
/Porta 4 (USB-C)/CC1: J401.A5 (CC1), R402.2
/Porta 4 (USB-C)/CC2: J401.B5 (CC2), R403.2
/Porta 4 (USB-C)/CONN_DN: J401.A7 (D-), J401.B7 (D-), U401.7 (C0-)
/Porta 4 (USB-C)/CONN_DP: J401.A6 (D+), J401.B6 (D+), U401.8 (C0+)
/Porta 4 (USB-C)/LED1_K: D402.2 (A), R406.2
/Porta 4 (USB-C)/SW_REF: C406.1, U401.6 (REF)
BTN_P2: C204.1, SW201.1; also elsewhere on the board
BTN_P3: C304.1, SW301.1; also elsewhere on the board
BTN_P4: C404.1, SW401.1; also elsewhere on the board
GND: C201.2, C202.2, C203.2, C204.2, C206.2, C301.2, C302.2, C303.2, C304.2, C306.2, C401.2, C402.2, C403.2, C404.2, C406.2, D202.1 (K), D302.1 (K), D402.1 (K), J201.A1 (GND), J201.A12 (GND), J201.B1 (GND), J201.B12 (GND), J201.SH (SHIELD), J301.A1 (GND), J301.A12 (GND), J301.B1 (GND), J301.B12 (GND), J301.SH (SHIELD), J401.A1 (GND), J401.A12 (GND), J401.B1 (GND), J401.B12 (GND), J401.SH (SHIELD), SW201.2, SW301.2, SW401.2, U201.5 (GND), U301.5 (GND), U401.5 (GND); also elsewhere on the board
HUB_DN2: U201.2 (L0-); also elsewhere on the board
HUB_DN3: U301.2 (L0-); also elsewhere on the board
HUB_DN4: U401.2 (L0-); also elsewhere on the board
HUB_DP2: U201.1 (L0+); also elsewhere on the board
HUB_DP3: U301.1 (L0+); also elsewhere on the board
HUB_DP4: U401.1 (L0+); also elsewhere on the board
LED_P2: R206.1; also elsewhere on the board
LED_P3: R306.1; also elsewhere on the board
LED_P4: R406.1; also elsewhere on the board
OE_N_P2: R204.2, U201.9 (EN); also elsewhere on the board
OE_N_P3: R304.2, U301.9 (EN); also elsewhere on the board
OE_N_P4: R404.2, U401.9 (EN); also elsewhere on the board
VBUS_P2: C202.1, C203.1, J201.A4 (VBUS), J201.A9 (VBUS), J201.B4 (VBUS), J201.B9 (VBUS), R202.1, R203.1; also elsewhere on the board
VBUS_P3: C302.1, C303.1, J301.A4 (VBUS), J301.A9 (VBUS), J301.B4 (VBUS), J301.B9 (VBUS), R302.1, R303.1; also elsewhere on the board
VBUS_P4: C402.1, C403.1, J401.A4 (VBUS), J401.A9 (VBUS), J401.B4 (VBUS), J401.B9 (VBUS), R402.1, R403.1; also elsewhere on the board

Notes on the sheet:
VBUS dagli UCS2114 (foglio hub), con limite di corrente, blocco inverso e scarica automatica integrati. Dati: PI3USB4002A tra hub e connettore, OE_N (EN) alto = scollegato (pull-up: scollegato al reset); lato connettore tollera 24 V e si apre da solo sopra 4,75 V.
LED: unico LED della porta, pilotato dal MCU: spento = disabilitata, acceso = abilitata, lampeggiante = guasto (D63).
la porta non lo impone: limite hw 2,5-2,9 A (UCS2114)
Rp 56 k: annuncio standard USB (500 mA);
